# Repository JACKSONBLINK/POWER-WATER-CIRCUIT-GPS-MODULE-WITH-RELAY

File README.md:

# POWER-WATER-CIRCUIT-GPS-MODULE-WITH-RELAY

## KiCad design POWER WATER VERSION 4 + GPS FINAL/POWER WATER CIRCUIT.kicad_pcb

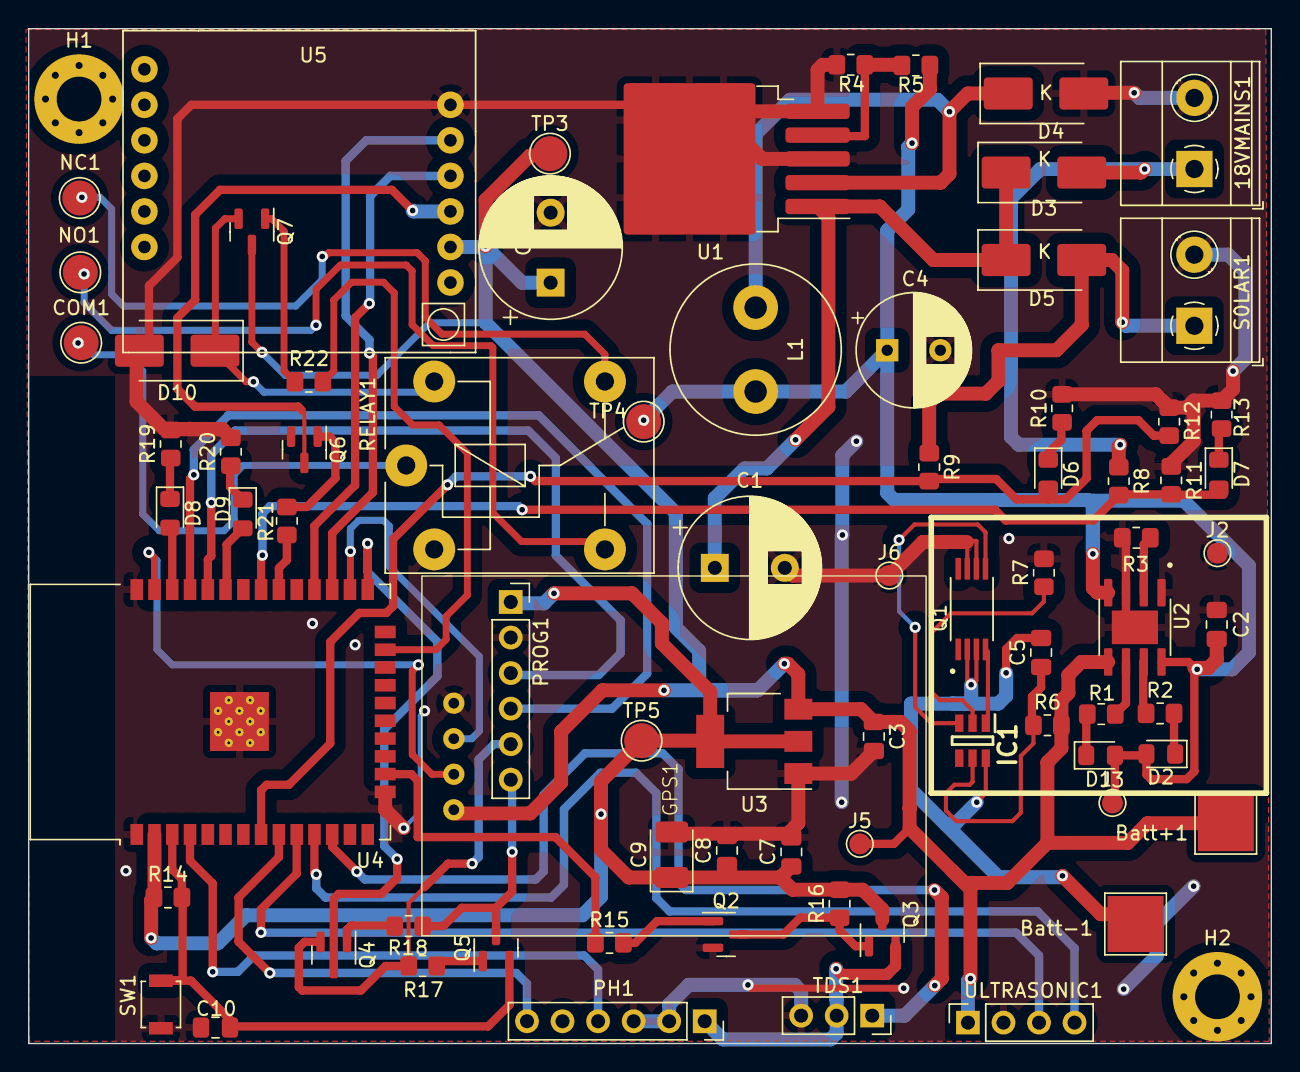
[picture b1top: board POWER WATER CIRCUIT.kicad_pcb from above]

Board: 2 copper layers, 88.8 x 72.5 mm, 79 parts (0 on the bottom side), 57 nets.

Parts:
18VMAINS1: Screw_Terminal_01x02; TerminalBlock_Phoenix_MKDS-1,5-2-5.08_1x02_P5.08mm_Horizont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
Batt+1: BatteryPositive; TestPoint_Pad_4.0x4.0mm
Batt-1: BatteryNegative; TestPoint_Pad_4.0x4.0mm
C1, C6: 470uF; CP_Radial_D10.0mm_P5.00mm
C2, C3, C5, C7, C8, C10: 0.1uF; C_0805_2012Metric_Pad1.18x1.45mm_HandSolder
C4: 220uF; CP_Radial_D8.0mm_P3.80mm
C9: 220uF; CP_EIA-3528-15_AVX-H_Pad1.50x2.35mm_HandSolder
COM1: TestPoint; TestPoint_Pad_D2.5mm
D1, D6, D8: GREEN_LED; LED_0805_2012Metric_Pad1.15x1.40mm_HandSolder
D2, D7, D9: RED_LED; LED_0805_2012Metric_Pad1.15x1.40mm_HandSolder
D3, D5, D10: 1N5820; D_SMB_Handsoldering
D4: 1N5819; D_SMB_Handsoldering
GPS1: gps_module
H1, H2: MountingHole_Pad; MountingHole_3.2mm_M3_Pad_Via
IC1: DW01; SOT95P280X135-6N
J2: IN-; TestPoint_Pad_D1.5mm
J3: IN+; TestPoint_Pad_D1.5mm
J5: OUT +; TestPoint_Pad_D1.5mm
J6: OUT -; TestPoint_Pad_D1.5mm
L1: 33uH; L_Radial_D12.0mm_P6.00mm_Murata_1900R
NC1: TestPoint; TestPoint_Pad_D2.5mm
NO1: TestPoint; TestPoint_Pad_D2.5mm
PH1: Conn_01x06_Socket; PinSocket_1x06_P2.54mm_Vertical
PROG1: Conn_01x06_Socket; PinSocket_1x06_P2.54mm_Vertical
Q1: FS8205A; SOP65P640X120-8N
Q2, Q4, Q5, Q6, Q7: BC817; SOT-23
Q3: IRLML5203; SOT-23
R1, R2, R4, R7: 1K; R_0805_2012Metric_Pad1.20x1.40mm_HandSolder
R3: 1.2K; R_0805_2012Metric_Pad1.20x1.40mm_HandSolder
R5: 3.9k; R_0805_2012Metric_Pad1.20x1.40mm_HandSolder
R6: 100; R_0805_2012Metric_Pad1.20x1.40mm_HandSolder
R8, R9: 10 K; R_0805_2012Metric_Pad1.20x1.40mm_HandSolder
R10, R13, R19, R20: 1k; R_0805_2012Metric_Pad1.20x1.40mm_HandSolder
R11, R12: 2.2 K; R_0805_2012Metric_Pad1.20x1.40mm_HandSolder
R14: 100K; R_0805_2012Metric_Pad1.20x1.40mm_HandSolder
R15: 10k; R_0805_2012Metric_Pad1.20x1.40mm_HandSolder
R16: 100k; R_0805_2012Metric_Pad1.20x1.40mm_HandSolder
R17, R18, R21, R22: 10K; R_0805_2012Metric_Pad1.20x1.40mm_HandSolder
RELAY1: FINDER-36.11; Relay_SPDT_Finder_36.11
S0LAR1: Screw_Terminal_01x02; TerminalBlock_Phoenix_MKDS-1,5-2-5.08_1x02_P5.08mm_Horizont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
SW1: SW_MEC_5G; SW_SPST_B3U-1000P
TDS1: Conn_01x03_Socket; PinSocket_1x03_P2.54mm_Vertical
TP3, TP4, TP5: TestPoint; TestPoint_Pad_D2.5mm
U1: LM2596S-ADJ; TO-263-5_TabPin3
U2: TP4056; SOP127P600X175-9N
U3: LM1117MP-3.3; SOT-223-3_TabPin2
U4: ESP32-WROOM-32
U5: SIM800L-CORE
ULTRASONIC1: Conn_01x04_Pin; PinSocket_1x04_P2.54mm_Vertical

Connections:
4.2: Batt+1.1, C3.1, C6.1, GPS1.1 (VCC), J5.1, Q7.3 (C), R6.2, TP3.1, U2.5 (BAT), U3.3 (VI), U5.2 (VCC), ULTRASONIC1.1
6V: C2.1, C4.1, D1.2 (A), D2.2 (A), J3.1, L1.2, R5.2, TP4.1, U2.4 (VCC), U2.8 (CE)
+3.3V: C7.1, C8.1, C9.1, PROG1.1, Q3.2 (S), R14.1, R16.2, TP5.1, U3.2 (VO), U4.2 (VDD)
+ 18 V: C1.1, D3.1 (K), D5.1 (K), U1.1 (VIN)
CHRG: R2.1, U2.7 (~CHRG)
COM: COM1.1, RELAY1.11
DC_Mains: 18VMAINS1.1, D3.2 (A), R8.1
DC_Solar: D5.2 (A), R9.1, S0LAR1.1
DTR: PROG1.5, Q4.2 (E), R17.1
GND: 18VMAINS1.2, C1.2, C2.2, C3.2, C4.2, C6.2, C7.2, C8.2, C9.2, C10.2, D4.2 (A), D10.2 (A), GPS1.4 (GND), J2.1, J6.1, PH1.2, PH1.3, PROG1.2, Q1.6 (S2_1), Q1.7 (S2_2), Q2.2 (E), Q6.2 (E), R3.1, R4.1, R7.2, R10.2, R11.1, R12.1, R13.2, R19.2, R20.2, RELAY1.A1, S0LAR1.2, SW1.2 (B), TDS1.3, U1.3 (GND), U1.5 (~ON/OFF), U2.1 (TEMP), U2.3 (GND), U2.9 (EP), U3.1 (GND), U4.1 (GND), U4.15 (GND), U4.38 (GND), U4.39 (GND), U5.6 (GND), ULTRASONIC1.2
GPIO0: Q4.3 (C), U4.25 (IO0)
GPS RX: GPS1.2 (RX), U4.37 (IO23)
GPS TX: GPS1.3 (TX), U4.26 (IO4)
GREEN_LED: D8.2 (A), U4.36 (IO22)
MCU_RX: PROG1.3, U4.34 (RXD0/IO3)
MCU_TX: PROG1.4, U4.35 (TXD0/IO1)
Mains_Available: D7.2 (A), R8.2, R11.2, U4.31 (IO19)
NC: NC1.1, RELAY1.12
NO: NO1.1, RELAY1.14
unnamed: D1.1 (K), R1.2
unnamed: D2.1 (K), R2.2
unnamed: D4.1 (K), L1.1, U1.2 (OUT)
unnamed: D6.1 (K), R10.1
unnamed: D7.1 (K), R13.1
unnamed: D8.1 (K), R19.1
unnamed: D9.1 (K), R20.1
unnamed: D10.1 (K), Q7.2 (E), RELAY1.A2
unnamed: IC1.2 (CSI), R7.1
unnamed: IC1.3 (OC), Q1.5 (G2)
unnamed: IC1.1 (OD), Q1.4 (G1)
unnamed: C5.1, IC1.5 (VDD), R6.1
unnamed: Batt-1.1, C5.2, IC1.6 (VSS), Q1.2 (S1_1), Q1.3 (S1_2)
unnamed: Q2.1 (B), R15.2
unnamed: Q2.3 (C), Q3.1 (G), R16.1
unnamed: Q4.1 (B), R18.2
unnamed: Q5.1 (B), R17.2
unnamed: Q6.1 (B), R21.2
unnamed: Q7.1 (B), R22.1
unnamed: R4.2, R5.1, U1.4 (FB)
unnamed: R3.2, U2.2 (PROG)
PH_Analog: PH1.4, U4.4 (SENSOR_VP)
RED_LED: D9.2 (A), U4.33 (IO21)
RESET: C10.1, Q5.2 (E), R14.2, SW1.1 (A), U4.3 (EN)
RL1: R22.2, U4.23 (IO15)
RTS: PROG1.6, Q5.3 (C), R18.1
SIM_RST: Q6.3 (C), U5.3 (RST)
SIM_RST_PIN: R21.1, U4.30 (IO18)
SIM_RX: U4.28 (IO17), U5.4 (RXD)
SIM_TX: U4.27 (IO16), U5.5 (TXD)
STDBY: R1.1, U2.6 (~STDBY)
Sen_pwr: R15.1, U4.16 (IO13)
Solar_Voltage: D6.2 (A), R9.2, R12.2, U4.8 (IO32)
Temp_Analog: PH1.6, U4.9 (IO33)
TurbidityAnalog: TDS1.1, U4.12 (IO27)
US_RX: U4.11 (IO26), ULTRASONIC1.4
US_TX: U4.10 (IO25), ULTRASONIC1.3
pwr: PH1.1, Q3.3 (D), TDS1.2

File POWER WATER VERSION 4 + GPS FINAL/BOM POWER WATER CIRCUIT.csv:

"Id;""Designator"";""Footprint"";""Quantity"";""Designation"";""Supplier and ref"";",,,,,
"1;""Q3"";""SOT-23"";1;""IRLML5203"";;;",,,,,
"2;""Q5",Q4,Q6,"Q2"";""SOT-23"";4;""BC817"";;;",,
"3;""C1","C6"";""CP_Radial_D10.0mm_P5.00mm"";2;""470uF"";;;",,,,
"4;""PROG1","PH1"";""PinSocket_1x06_P2.54mm_Vertical"";2;""Conn_01x06_Socket"";;;",,,,
"5;""R17",R21,"R18"";""R_0805_2012Metric_Pad1.20x1.40mm_HandSolder"";3;""10K"";;;",,,
"6;""J3"";""TestPoint_Pad_D1.5mm"";1;""IN+"";;;",,,,,
"7;""L1"";""L_Radial_D12.0mm_P6.00mm_Murata_1900R"";1;""33uH"";;;",,,,,
"8;""D1",D8,"D6"";""LED_0805_2012Metric_Pad1.15x1.40mm_HandSolder"";3;""GREEN_LED"";;;",,,
"9;""C4"";""CP_Radial_D8.0mm_P3.80mm"";1;""220uF"";;;",,,,,
"10;""C9"";""CP_EIA-3528-15_AVX-H_Pad1.50x2.35mm_HandSolder"";1;""220uF"";;;",,,,,
"11;""H1","H2"";""MountingHole_3.2mm_M3_Pad_Via"";2;""MountingHole_Pad"";;;",,,,
"12;""U2"";""SOP127P600X175-9N"";1;""TP4056"";;;",,,,,
"13;""R2",R7,R1,"R4"";""R_0805_2012Metric_Pad1.20x1.40mm_HandSolder"";4;""1K"";;;",,
"14;""SW1"";""SW_SPST_B3U-1000P"";1;""SW_MEC_5G"";;;",,,,,
"15;""IC1"";""SOT95P280X135-6N"";1;""DW01"";;;",,,,,
"16;""C10",C8,C5,C2,C3,"C7"";""C_0805_2012Metric_Pad1.18x1.45mm_HandSolder"";6;""0.1uF"";;;"
"17;""U1"";""TO-263-5_TabPin3"";1;""LM2596S-ADJ"";;;",,,,,
"18;""R5"";""R_0805_2012Metric_Pad1.20x1.40mm_HandSolder"";1;""3.9k"";;;",,,,,
"19;""R11","R12"";""R_0805_2012Metric_Pad1.20x1.40mm_HandSolder"";2;""2.2 K"";;;",,,,
"20;""TDS1"";""PinSocket_1x03_P2.54mm_Vertical"";1;""Conn_01x03_Socket"";;;",,,,,
"21;""S0LAR1","18VMAINS1"";""TerminalBlock_Phoenix_MKDS-1","5-2-5.08_1x02_P5.08mm_Horizontal"";2;""Screw_Terminal_01x02"";;;",,,
"22;""D2",D9,"D7"";""LED_0805_2012Metric_Pad1.15x1.40mm_HandSolder"";3;""RED_LED"";;;",,,
"23;""J2"";""TestPoint_Pad_D1.5mm"";1;""IN-"";;;",,,,,
"24;""R6"";""R_0805_2012Metric_Pad1.20x1.40mm_HandSolder"";1;""100"";;;",,,,,
"25;""D3","D5"";""D_SMB_Handsoldering"";2;""1N5820"";;;",,,,
"26;""R16"";""R_0805_2012Metric_Pad1.20x1.40mm_HandSolder"";1;""100k"";;;",,,,,
"27;""ULTRASONIC1"";""PinSocket_1x04_P2.54mm_Vertical"";1;""Conn_01x04_Pin"";;;",,,,,
"28;""TP5",TP4,"TP3"";""TestPoint_Pad_D2.5mm"";3;""TestPoint"";;;",,,
"29;""TP1"";""TestPoint_Pad_4.0x4.0mm"";1;""BatteryPositive"";;;",,,,,
"30;""R9","R8"";""R_0805_2012Metric_Pad1.20x1.40mm_HandSolder"";2;""10 K"";;;",,,,
"31;""U3"";""SOT-223-3_TabPin2"";1;""LM1117MP-3.3"";;;",,,,,
"32;""R15"";""R_0805_2012Metric_Pad1.20x1.40mm_HandSolder"";1;""10k"";;;",,,,,
"33;""U4"";""ESP32-WROOM-32"";1;""ESP32-WROOM-32"";;;",,,,,
"34;""U5"";""SIM800L-CORE"";1;""SIM800L-CORE"";;;",,,,,
"35;""TP2"";""TestPoint_Pad_4.0x4.0mm"";1;""BatteryNegative"";;;",,,,,
"36;""D4"";""D_SMB_Handsoldering"";1;""1N5819"";;;",,,,,
"37;""R20",R19,R10,"R13"";""R_0805_2012Metric_Pad1.20x1.40mm_HandSolder"";4;""1k"";;;",,
"38;""J5"";""TestPoint_Pad_D1.5mm"";1;""OUT +"";;;",,,,,
"39;""R14"";""R_0805_2012Metric_Pad1.20x1.40mm_HandSolder"";1;""100K"";;;",,,,,
"40;""R3"";""R_0805_2012Metric_Pad1.20x1.40mm_HandSolder"";1;""1.2K"";;;",,,,,
"41;""J6"";""TestPoint_Pad_D1.5mm"";1;""OUT -"";;;",,,,,
"42;""Q1"";""SOP65P640X120-8N"";1;""FS8205A"";;;",,,,,

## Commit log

2024-06-29 POWER WATER CIRCUIT ADDED GPS MODULE AND RELAY
